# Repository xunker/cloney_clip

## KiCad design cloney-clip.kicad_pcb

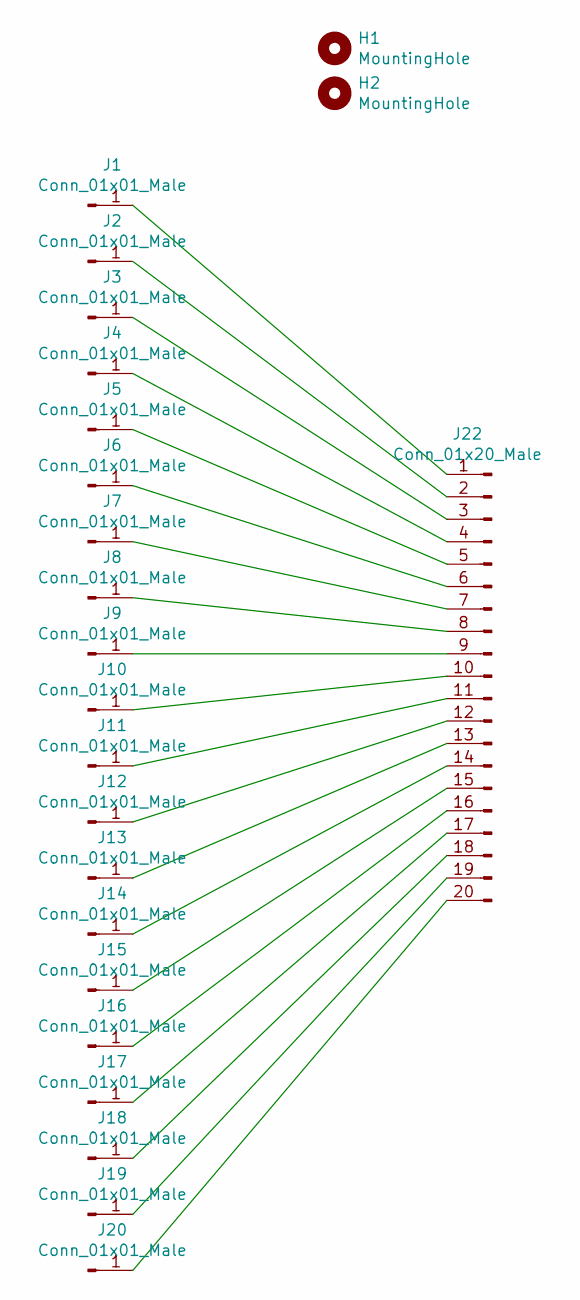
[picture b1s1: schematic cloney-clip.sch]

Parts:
H1, H2: MountingHole; MountingHole_1.7mm_no_courtyard
J1, J2, J3, J4, J5, J6, J7, J8, J9, J10, J11, J12, J13, J14, J15, J16, J17, J18, J19, J20: Conn_01x01_Male; TE_2306334
J22: Conn_01x20_Male; PinHeader_1x20_P2.54mm_Vertical

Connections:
unnamed: J1.1, J22.1
unnamed: J2.1, J22.2
unnamed: J10.1, J22.10
unnamed: J11.1, J22.11
unnamed: J12.1, J22.12
unnamed: J13.1, J22.13
unnamed: J14.1, J22.14
unnamed: J15.1, J22.15
unnamed: J16.1, J22.16
unnamed: J17.1, J22.17
unnamed: J18.1, J22.18
unnamed: J19.1, J22.19
unnamed: J20.1, J22.20
unnamed: J3.1, J22.3
unnamed: J4.1, J22.4
unnamed: J5.1, J22.5
unnamed: J6.1, J22.6
unnamed: J7.1, J22.7
unnamed: J8.1, J22.8
unnamed: J9.1, J22.9

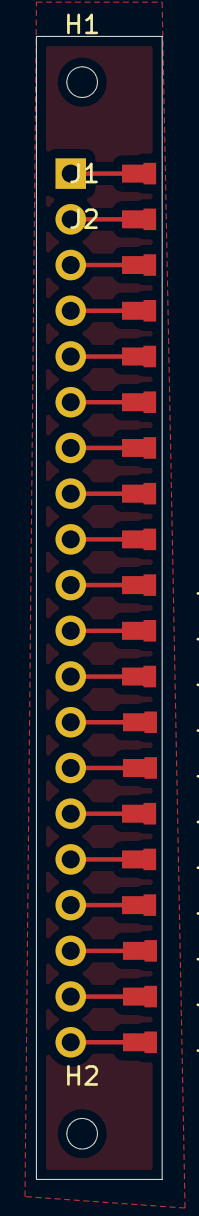
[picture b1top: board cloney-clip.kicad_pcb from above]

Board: 2 copper layers, 7.0 x 63.5 mm, 23 parts (1 on the bottom side), 20 nets.

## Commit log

2021-06-01 initial commit after some work
2021-06-01 Add annotatied diagram for mill max 0965
2021-06-01 add exported footprints for sprigns and pogos
